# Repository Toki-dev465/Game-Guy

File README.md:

# Game-Guy
A compact handheld console featuring a 0.96 inch OLED display, a passive piezo buzzer for sound effects, D-pad, and A and B buttons. It is powered by an LiPo battery and the XIAO RP2350 microcontroller. Right now, the only game is flappy bird. Simply tap A or B to flap the bird. 

# BOM
- 1x XIAO RP2350 https://www.digikey.ca/en/products/detail/seeed-technology-co-ltd/102010550/24814463
- 6x TS02 tactile switch https://www.digikey.ca/en/products/detail/same-sky-formerly-cui-devices/TS02-66-60-BK-160-LCR-D/15634268
- 1x I2C OLED Display Module 0.96 Inch SSD1306 https://www.aliexpress.com/item/1005009180825215.html?src=google&pdp_npi=4%40dis!CAD!5.54!5.54!!!!!%40!12000048217113638!ppc!!! 
- 1x Piezo buzzer https://www.digikey.com/en/products/detail/tdk/PS1240P02BT/935924 
- 1x Lithium-Ion Polymer (LiPo) Battery (3.7V 110mAh) https://www.canadarobotix.com/products/939
- 1x Slide switch https://www.digikey.ca/en/products/detail/c-k/OS102011MA1QN1/1981430

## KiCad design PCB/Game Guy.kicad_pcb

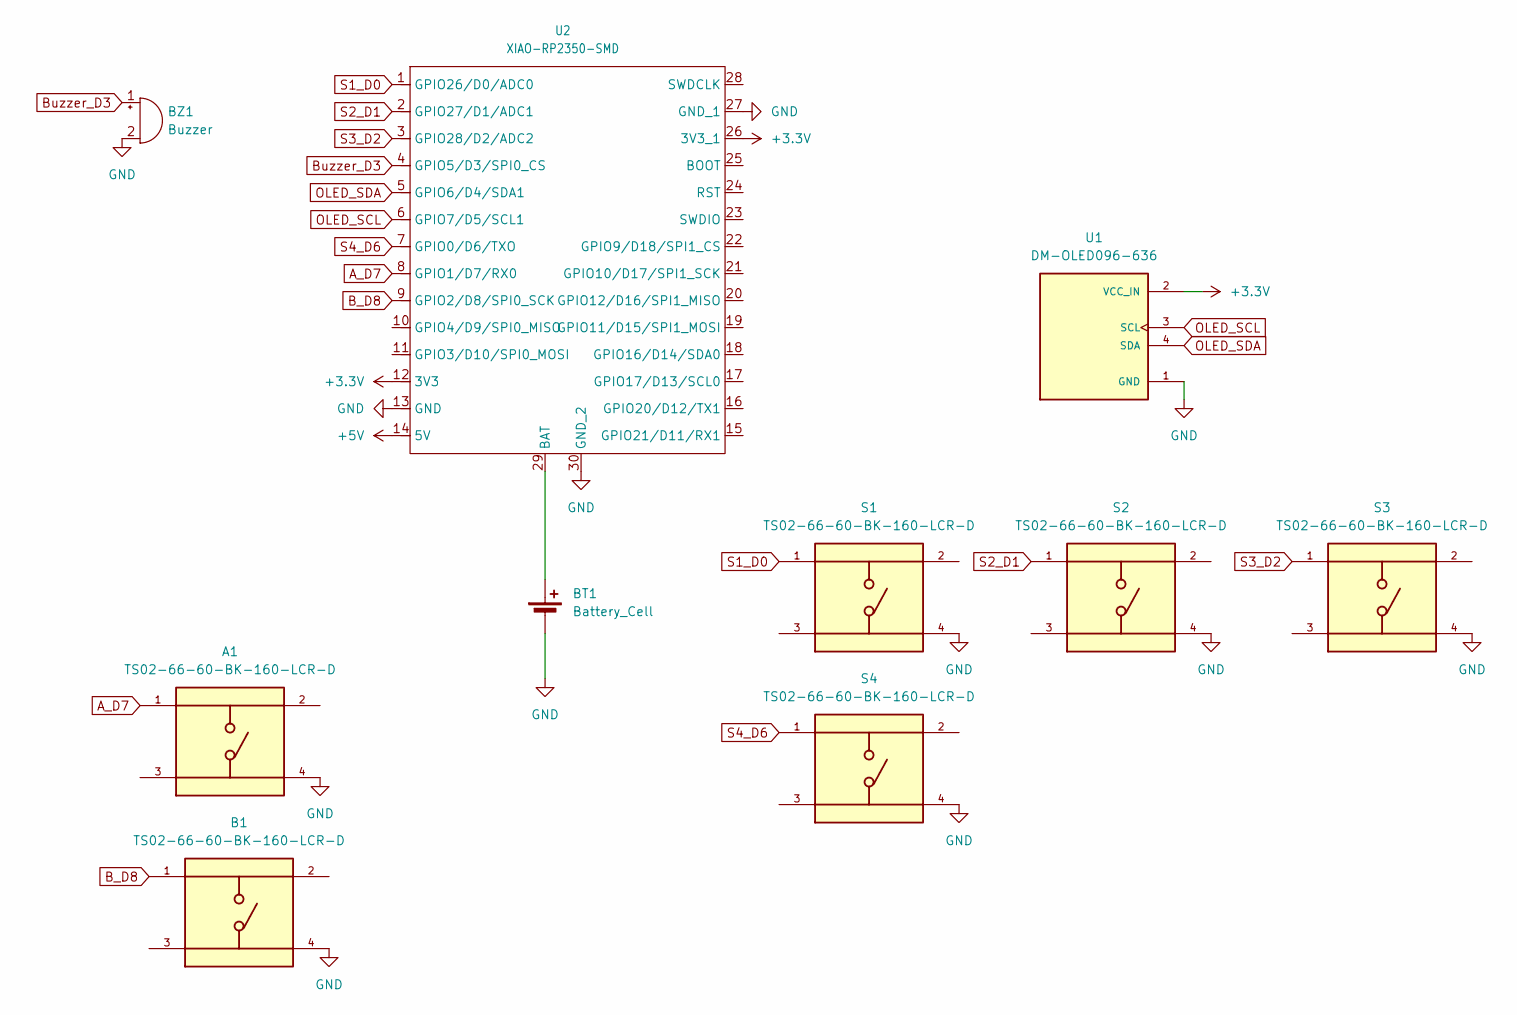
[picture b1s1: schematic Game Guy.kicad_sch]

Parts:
A1: TS02-66-60-BK-160-LCR-D; SW_TS02-66-60-BK-160-LCR-D; PARTREV 1.0
B1: TS02-66-60-BK-160-LCR-D; SW_TS02-66-60-BK-160-LCR-D; PARTREV 1.0
BT1: Battery_Cell
BZ1: Buzzer; Buzzer_TDK_PS1240P02BT_D12.2mm_H6.5mm
S1, S2, S3, S4: TS02-66-60-BK-160-LCR-D; SW_TS02-66-60-BK-160-LCR-D; PARTREV 1.0
U1: DM-OLED096-636; MODULE_DM-OLED096-636; PARTREV 2018-09-10
U2: XIAO-RP2350-SMD; XIAO-RP2350-DIP

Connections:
+3.3V: U1.2 (VCC_IN), U2.12 (3V3), U2.26 (3V3_1)
+5V: U2.14 (5V)
A_D7: A1.1, U2.8 (GPIO1/D7/RX0)
B_D8: B1.1, U2.9 (GPIO2/D8/SPI0_SCK)
Buzzer_D3: BZ1.1 (+), U2.4 (GPIO5/D3/SPI0_CS)
GND: A1.4, B1.4, BT1.2 (-), BZ1.2 (-), S1.4, S2.4, S3.4, S4.4, U1.1 (GND), U2.13 (GND), U2.27 (GND_1), U2.30 (GND_2)
unnamed: BT1.1 (+), U2.29 (BAT)
OLED_SCL: U1.3 (SCL), U2.6 (GPIO7/D5/SCL1)
OLED_SDA: U1.4 (SDA), U2.5 (GPIO6/D4/SDA1)
S1_D0: S1.1, U2.1 (GPIO26/D0/ADC0)
S2_D1: S2.1, U2.2 (GPIO27/D1/ADC1)
S3_D2: S3.1, U2.3 (GPIO28/D2/ADC2)
S4_D6: S4.1, U2.7 (GPIO0/D6/TXO)

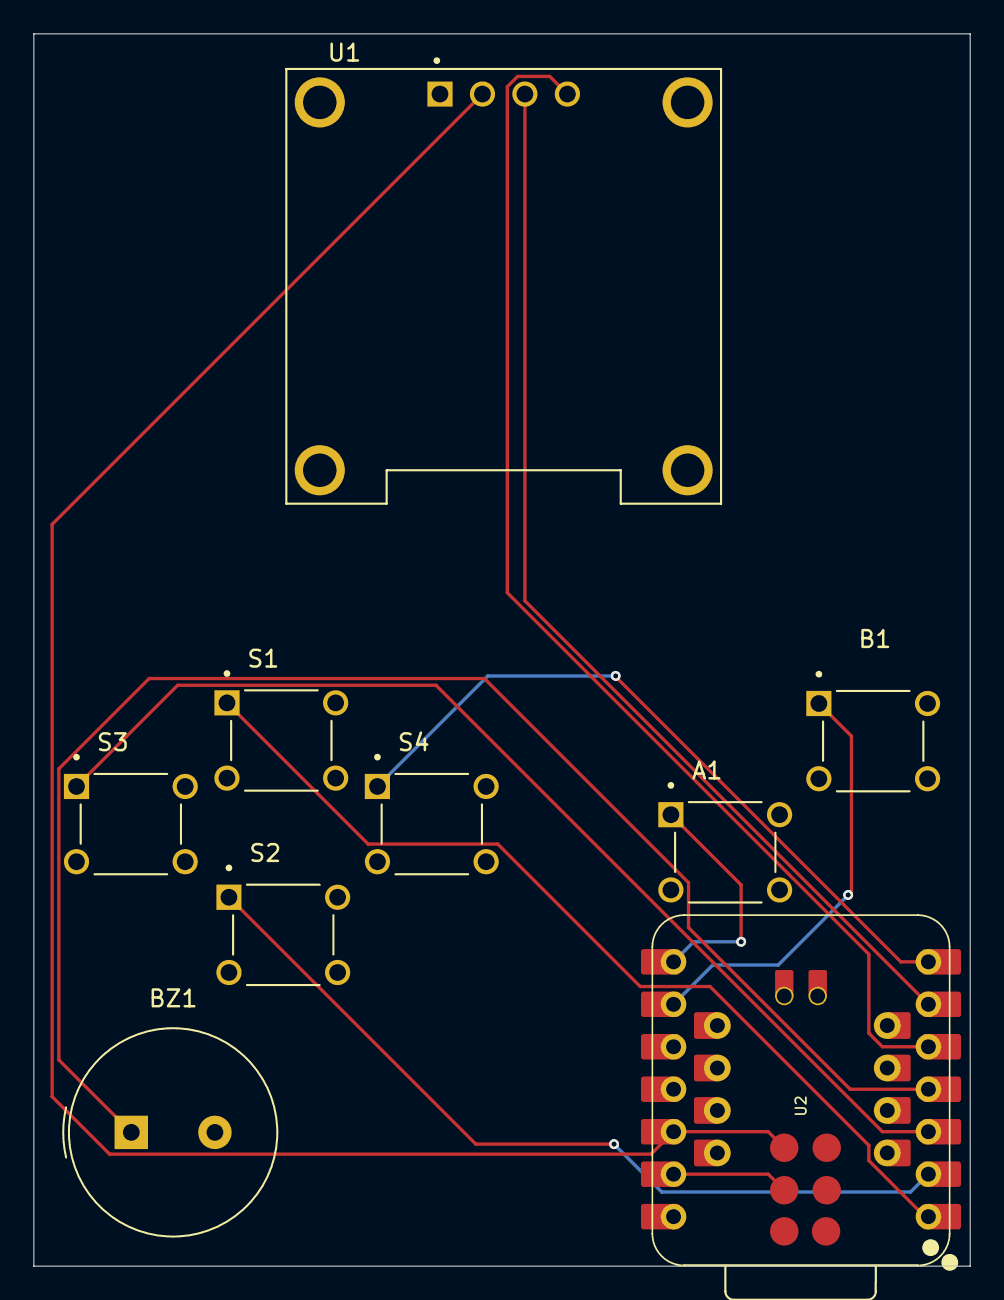
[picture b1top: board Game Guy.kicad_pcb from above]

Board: 2 copper layers, 56.0 x 73.7 mm, 9 parts (0 on the bottom side), 11 nets.
